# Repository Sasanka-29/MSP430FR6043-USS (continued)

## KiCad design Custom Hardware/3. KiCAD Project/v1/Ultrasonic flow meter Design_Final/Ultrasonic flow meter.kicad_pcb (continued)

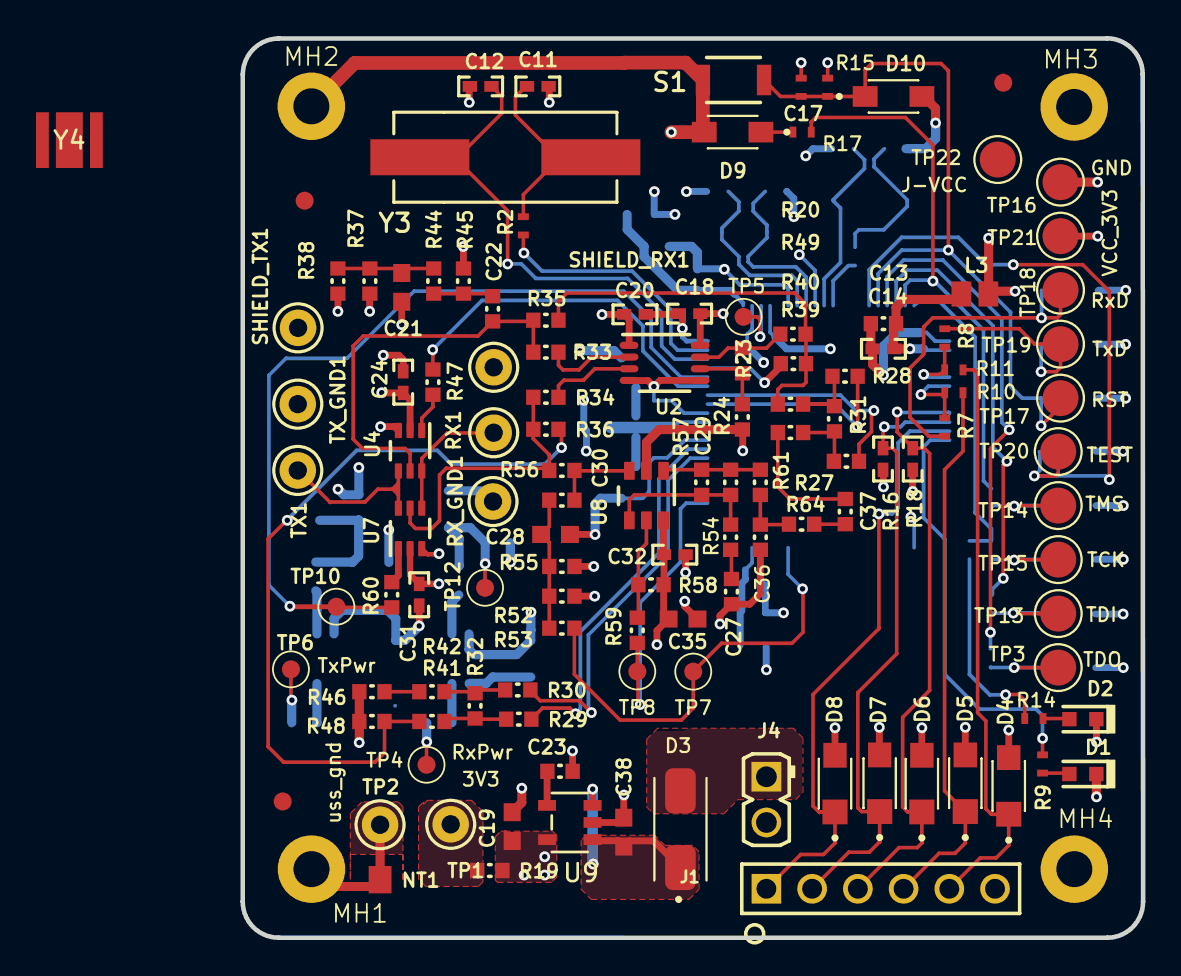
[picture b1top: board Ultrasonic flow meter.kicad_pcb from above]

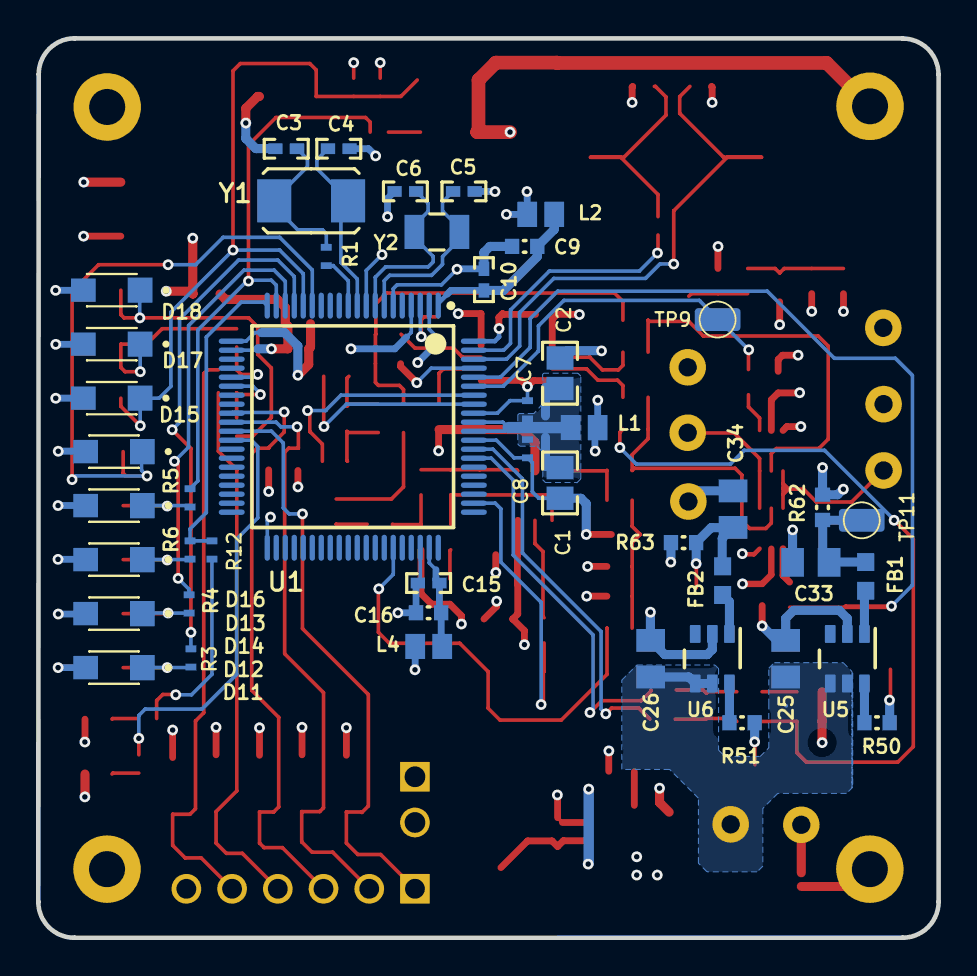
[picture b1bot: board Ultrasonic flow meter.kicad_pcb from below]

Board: 4 copper layers, 50.0 x 50.0 mm, 171 parts (46 on the bottom side), 90 nets.

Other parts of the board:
Y4: Crystal; AWSCR-8.00CV-T_ABR

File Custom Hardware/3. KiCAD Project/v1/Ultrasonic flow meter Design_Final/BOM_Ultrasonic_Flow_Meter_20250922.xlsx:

# | Reference | Qty | DNP | Value | Description | Footprint | Exclude from BOM | Exclude from Board
1 | C23 | 1 |  | C0603C471J5GACTU | CAP, CERM, 470 pF, 50 V, +/- 5%, C0G/NP0, 0603 | ultrasonicFM:0603L
2 | C29 | 1 |  | C0603C330J5GACTU | CAP, CERM, 33 pF, 50 V, +/- 5%, C0G/NP0, 0603 | ultrasonicFM:0603L
3 | C36 | 1 |  | C0603C681J5GACTU | CAP, CERM, 680 pF, 50 V, +/- 5%, C0G/NP0, 0603 | ultrasonicFM:0603L
4 | C37 | 1 |  | CC0603KRX7R7BB102 | CAP, CERM, 1000 pF, 16 V,+/- 10%, X7R, 0603 | ultrasonicFM:0603L
5 | C1,C2 | 2 |  | C2012X5R1A336M125AC | CAP, CERM, 33 uF, 10 V, +/- 20%, X5R, 0805 | ultrasonicFM:0805
6 | C10,C14,C15,C18,C20,C24,C31,C32 | 8 |  | GRM155R71C104KA88D | CAP, CERM, 0.1 uF, 16 V, +/- 10%, X7R, 0402 | ultrasonicFM:0402
7 | C19,C21,C28,C35,C38 | 5 |  | GRM188R61C225KE15D | CAP, CERM, 2.2 uF, 16 V, +/- 10%, X5R, 0603 | ultrasonicFM:0603
8 | C25,C26 | 2 |  | CL21B106KPQNNNE | CAP, CERM, 10 uF, 10 V, +/- 10%, X5R, 0805 | ultrasonicFM:0805_HV
9 | C3,C4,C5,C6,C11,C12 | 6 |  | GRM1555C1H120JA01D | CAP, CERM, 12 pF, 50 V, +/- 5%, C0G/NP0, 0402 | ultrasonicFM:0402
10 | C33,C34 | 2 |  | GRM21BR61C105KA01L | CAP, CERM, 1 uF, 16 V, +/- 10%, X5R, 0805 | ultrasonicFM:0805_HV
11 | C7,C8,C17 | 3 |  | GRM1555C1H102JA01D | CAP, CERM, 1000 pF, 50 V, +/- 5%, C0G/NP0, 0402 | ultrasonicFM:0402S
12 | C9,C13,C16,C22,C27,C30 | 6 |  | CL10B105KO8NNNC | CAP, CERM, 1 uF, 16 V, +/- 10%, X7R, 0603 | ultrasonicFM:0603L
13 | D3 | 1 |  | CDBA340L-HF | DIODE SCHOTTKY 40V 3A DO214AC | ultrasonicFM:DIOM5225X250N
14 | D1,D2 | 2 |  | LTST-C191TGKT | LED, Green, SMD | ultrasonicFM:LTST-C191_Green
15 | D4,D5,D6,D7,D8,D9,D10,D11,D12,D13,D14,D15,D16,D17,D18 | 15 |  | SMF5.0A | TVS DIODE 5VWM 9.2VC SOD123 | ultrasonicFM:SOD3718X102N
16 | FB1,FB2 | 2 |  | MPZ1608S221A | Ferrite Bead, 220 ohm @ 100 MHz, 2.2 A, 0603 | ultrasonicFM:0603
17 | FID1,FID2,FID3 | 3 |  | Fiducial | Fiducial mark. There is nothing to buy or mount. | ultrasonicFM:Fiducial10-30 | Excluded from BOM
18 | J1 | 1 |  | 61300611121 | 6 pins, 1 row, straight, gold plating | ultrasonicFM:61300611121
19 | J4 | 1 |  | 61300211121 | Header, 2.54 mm, 2x1, Gold, TH | ultrasonicFM:WURTH_61300211121
20 | L1,L2,L3,L4 | 4 |  | MPZ2012S601A | Ferrite Bead, 600 ohm @ 100 MHz, 2 A, 0805 | ultrasonicFM:0805L
21 | MH1,MH2,MH3,MH4 | 4 |  | MountingHole_Pad | Mounting Hole with connection | ultrasonicFM:M2_MH | Excluded from BOM
22 | NT1 | 1 |  | Net-Tie | Single point connection between nets. | ultrasonicFM:Net-Tie_50milWide_30milLong | Excluded from BOM
23 | R15 | 1 |  | CRCW040247K0JNED | RES, 47 k, 5%, 0.063 W, 0402 | ultrasonicFM:0402S
24 | R45 | 1 | DNP | RC0603FR-07200KL | RES, 200 k, 1%, 0.1 W, 0603 | ultrasonicFM:0603L
25 | R54 | 1 |  | RC0603FR-0710RL | RES, 10.0, 1%, 0.1 W, 0603 | ultrasonicFM:0603L
26 | R57 | 1 |  | RC0603FR-131K82L | RES, 1.82 k, 1%, 0.1 W, 0603 | ultrasonicFM:0603L
27 | R58 | 1 | DNP | RCG060310K0FKEA | RES, 10.0 k, 1%, 0.1 W, 0603 | ultrasonicFM:0603L
28 | R61 | 1 |  | RC0603FR-07499RL | RES, 499, 1%, 0.1 W, 0603 | ultrasonicFM:0603L
29 | R1,R2 | 2 |  | CRCW040222R0JNED | RES, 22, 5%, 0.063 W, 0402 | ultrasonicFM:0402S
30 | R16,R18 | 2 |  | RK73H1ETTP3301F | RES, 3.30 k, 1%, 0.1 W, AEC-Q200 Grade 0, 0402 | ultrasonicFM:0402
31 | R19,R20,R24,R27,R28,R29,R30,R39,R40,R41,R47,R50,R51,R59,R60,R62,R63,R64 | 18 |  | RC0603FR-130RL | RES, 0, 5%, 0.1 W, 0603 | ultrasonicFM:0603L
32 | R23,R31,R32,R42,R53 | 5 | DNP | RC0603FR-130RL | RES, 0, 5%, 0.1 W, 0603 | ultrasonicFM:0603L
33 | R3,R4,R5,R6,R7,R8,R10,R11,R12,R17 | 10 |  | CRCW04020000Z0ED | RES, 0, 5%, 0.063 W, 0402 | ultrasonicFM:0402S
34 | R33,R34 | 2 |  | RC0603FR-07806RL | RES, 806, 1%, 0.1 W, 0603 | ultrasonicFM:0603L
35 | R35,R36 | 2 | DNP | RC0603FR-07806RL | RES, 806, 1%, 0.1 W, 0603 | ultrasonicFM:0603L
36 | R37,R38,R52,R55 | 4 |  | RC0603FR-072ML | RES, 2.00 M, 1%, 0.1 W, 0603 | ultrasonicFM:0603L
37 | R44,R56 | 2 |  | RC0603FR-0724K9L | RES, 24.9 k, 1%, 0.1 W, 0603 | ultrasonicFM:0603L
38 | R46,R48,R49 | 3 |  | RC0603FR-101ML | RES, 1.00 M, 1%, 0.1 W, 0603 | ultrasonicFM:0603L
39 | R9,R14 | 2 |  | CRCW0402390RJNED | RES, 390, 5%, 0.063 W, 0402 | ultrasonicFM:0402S
40 | RX1,TP1,TX1 | 3 |  | 5003 | Test Point, Miniature, Orange, TH | ultrasonicFM:Keystone5003
41 | RX_GND1,SHIELD_RX1,SHIELD_TX1,TP2,TX_GND1 | 5 |  | 5001 | Test Point, Miniature, Black, TH | ultrasonicFM:Keystone5001
42 | S1,S2 | 2 |  | B3U-1000P | SWITCH TACTILE SPST-NO 0.05A 12V | ultrasonicFM:SW_B3U-1000P
43 | TP3,TP13,TP14,TP15,TP16,TP17,TP18,TP19,TP20,TP21,TP22 | 11 |  |  | Test Point, SMD, 2MM | ultrasonicFM:TP_2MM | Excluded from BOM
44 | TP4,TP5,TP6,TP7,TP8,TP9,TP10,TP11,TP12 | 9 |  |  | Test Point, SMD, 1MM | ultrasonicFM:TP_1mm | Excluded from BOM
45 | U1 | 1 |  | MSP430FR6043IPN | Mixed-Signal Microcontroller, PN0080A (LQFP-80) | ultrasonicFM:PN0080A_N
46 | U2 | 1 |  | SN74LVC2T45DCTR | Dual-Bit Dual-Supply Bus Transceiver With Configurable Voltage Translation and 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 | ultrasonicFM:DCT0008A_N
47 | U8 | 1 |  | OPA836IDBVT | Very Low Power, Rail to Rail Out, Negative Rail In, VFB Operational Amplifier, 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 | ultrasonicFM:DBV0006A_N
48 | U9 | 1 |  | MIC5219-3.3YM5-TR | IC REG LINEAR 3.3V 500MA SOT23-5 | ultrasonicFM:SOT-23-5_M5_MCH-L
49 | U4,U7 | 2 |  | TS5A9411DCKR | 10-惟 SPDT ANALOG SWITCH SINGLE-CHANNEL 2:1 MULTIPLEXER/DEMULTIPLEXER, DCK0006A | ultrasonicFM:DCK0006A_N
50 | U5,U6 | 2 |  | TPS22860DBVR | Ultra-Low Leakage Load Switch, DBV0006A | ultrasonicFM:DBV0006A_N
51 | Y1 | 1 |  | ABM3-8.000MHZ-D2Y-T | Crystal, 8MHz, SMD | ultrasonicFM:Abracon_ABM3
52 | Y2 | 1 |  | ABS07-32.768KHZ-9-T | CRYSTAL, 32.768KHZ, 9PF, SMD | ultrasonicFM:XTAL_ABS07
53 | Y3 | 1 |  | ABLS-8.000MHZ-B4-T | Crystal, 8 MHz, 18pF, SMD | ultrasonicFM:XTAL_CSM-7X

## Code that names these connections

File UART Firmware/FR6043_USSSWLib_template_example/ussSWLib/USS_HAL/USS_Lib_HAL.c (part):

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    USSSWLIB_HAL_AFE_RXEN_PORT &= ~(USSSWLIB_HAL_AFE_RXEN_PIN);
    USSSWLIB_HAL_AFE_RXEN_PORT_DIR |= (USSSWLIB_HAL_AFE_RXEN_PIN);

    // Initialize RxSel1 and RxSel2 gpios (clear gpio and configure as output)
    USSSWLIB_HAL_AFE_RX_SELx_PORT &= ~(USSSWLIB_HAL_AFE_RX_SEL1_PIN
            | USSSWLIB_HAL_AFE_RX_SEL2_PIN);
    USSSWLIB_HAL_AFE_RX_SELx_PORT_DIR |= (USSSWLIB_HAL_AFE_RX_SEL1_PIN
            | USSSWLIB_HAL_AFE_RX_SEL2_PIN);

    // Initialize RxPwr gpios (set gpio and configure as output)
    // RxPwr is expected to be on all the time
    USSSWLIB_HAL_AFE_RXPWR_PORT |= (USSSWLIB_HAL_AFE_RXPWR_PIN);
    USSSWLIB_HAL_AFE_RXPWR_PORT_DIR |= (USSSWLIB_HAL_AFE_RXPWR_PIN);

#if (__EVM430_VER__ == 0x20)
    // Initialize TxPwr gpios (clear gpio and configure as output)
    USSSWLIB_HAL_AFE_TXPWR_PORT &= ~(USSSWLIB_HAL_AFE_TXPWR_PIN);
    USSSWLIB_HAL_AFE_TXPWR_PORT_DIR |= (USSSWLIB_HAL_AFE_TXPWR_PIN);

#if defined(__AFE_EXT_5v0__)
    // Initialize TxPwr gpios (clear gpio and configure as output)
    USSSWLIB_HAL_AFE_TX5VEN_PORT &= ~(USSSWLIB_HAL_AFE_TX5VEN_PIN);
    USSSWLIB_HAL_AFE_TX5VEN_PORT_DIR |= (USSSWLIB_HAL_AFE_TX5VEN_PIN);
#endif
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
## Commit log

2026-03-06 Add project title to README
2026-03-06 Update README.md with project information
2026-03-06 updated the readme file
2026-03-06 docs: add professional UART module README with flowchart
2026-03-06 Added flow chart
2026-03-06 Added another flow chart
2026-03-06 docs: enhance root README with badges, updated structure, links, and contributing section
2026-03-06 Updated multipple files
2026-03-07 Updated multipe files
2026-03-09 GUI Updated
2026-03-09 Updated GUI
2026-03-09 Added baseline calibration and Inhale/Exhale graphs in GUI
2026-03-12 CHanged GUI
2026-03-13 Minor changes in flowchart
2026-03-13 Change the flowchart to mermaid code
2026-03-13 Removed the unwanted zip file
2026-03-13 readme file
2026-03-16 Update README.md to reflect Spirometer GUI features
2026-03-16 Remove obsolete tempCodeRunnerFile.python reference from README
2026-03-16 Updated the UART Gui
2026-04-11 Auto-commit: 2026-04-11 - UART/uart_gui.py
2026-04-17 Rename project from 'Incentive Spirometer' to 'Spirometer'
2026-04-21 Added multiple things
2026-04-21 Added UART Firmware
2026-04-21 Update baud-rate setting in README
2026-05-03 Update README to mark PCB tasks as complete
